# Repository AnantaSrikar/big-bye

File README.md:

# big-bye
A project that encompasses (almost) all the knowledge and skills I acquired throughout my undergraduate degree, serving as a farewell gift! 

The skills / tools I used
- Programming (C. Python, bash, etc)
- Server Setup (Web server with HTTPS by Caddy)
- Network Setup (Its currently hosted on my HomeLab)
- Soldering (Perfboard and SMD)
- PCB Desigining
- 3D Modelling (A case was supposed to be designed, didn't happen due to logistical issues)

## Components
- [Firmware](/firmware/)
- [Web Server](/web_server/)

You can find a demo of the project [here](https://youtu.be/nfPE4j3Xo48)!

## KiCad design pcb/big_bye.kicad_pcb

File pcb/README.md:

# PCB
Here are the KiCAD files for the PCB that I designed for this project.

You can find the BOM [here](bom.csv).

The ST7735 Display can be found at this [link](https://robu.in/product/1-8-inch-spi-128160-tft-lcd-display-module-pcb-arduino/).

## Schematic

The PCB looks something like this:

You can watch a demo of the project in action (with the PCB and the display) [here](https://youtu.be/nfPE4j3Xo48)!

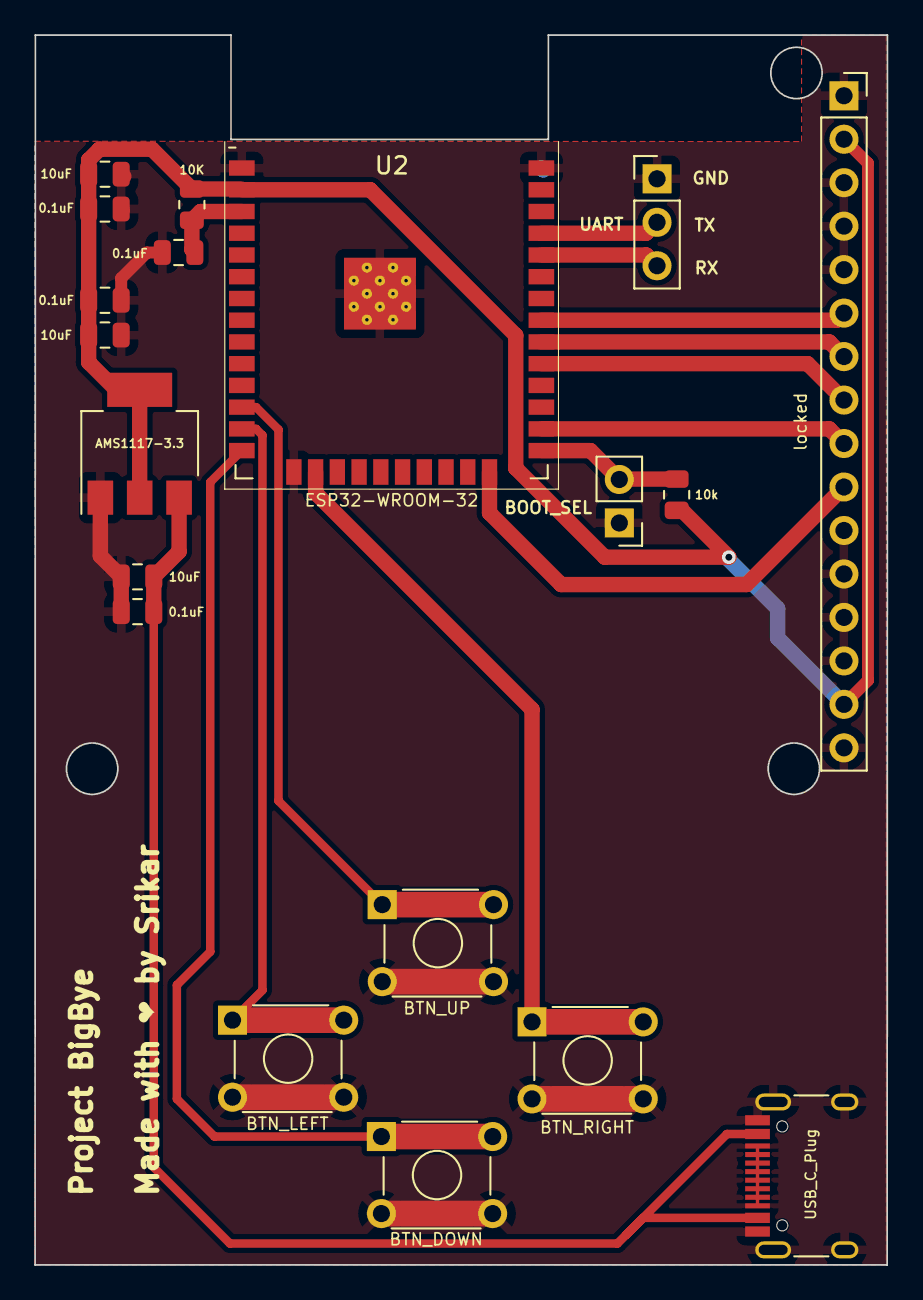
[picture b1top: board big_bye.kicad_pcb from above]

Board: 2 copper layers, 49.8 x 71.9 mm, 19 parts (0 on the bottom side), 16 nets.

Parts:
C1, C5, C7: 10uF; C_0805_2012Metric
C2, C3, C4, C6: 0.1uF; C_0805_2012Metric
J1: UART; PinHeader_1x03_P2.54mm_Vertical
J2: BOOT_SEL; PinHeader_1x02_P2.54mm_Vertical
J3: locked; PinSocket_1x16_P2.54mm_Vertical
P1: USB_C_Plug; USB_C_Receptacle_HRO_TYPE-C-31-M-12
R1: 10K; R_0805_2012Metric
R2: 10k; R_0805_2012Metric
SW1: BTN_LEFT; SW_TH_Tactile_Omron_B3F-10xx
SW2: BTN_RIGHT; SW_TH_Tactile_Omron_B3F-10xx
SW3: BTN_UP; SW_TH_Tactile_Omron_B3F-10xx
SW4: BTN_DOWN; SW_TH_Tactile_Omron_B3F-10xx
U1: AMS1117-3.3; SOT-223-3_TabPin2
U2: ESP32-WROOM-32

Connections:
+5V: C4.1, C5.1, P1.A4 (VBUS), P1.A9 (VBUS), P1.B4 (VBUS), P1.B9 (VBUS), U1.3 (VI)
BOOT: J2.2, R2.2, U2.25 (IO0)
BTN_DOWN: SW4.1, U2.14 (IO12)
BTN_LEFT: SW1.1, U2.13 (IO14)
BTN_RIGHT: SW2.1, U2.16 (IO13)
BTN_UP: SW3.1, U2.12 (IO27)
CS: J3.10, U2.24 (IO2)
DC: J3.7, U2.30 (IO18)
EN: C3.2, R1.1, U2.3 (EN)
GND: C1.2, C2.2, C3.1, C4.2, C5.2, C6.2, C7.2, J1.1, J2.1, J3.1, J3.3, J3.4, J3.5, J3.11, J3.12, J3.13, J3.14, J3.16, P1.A1 (GND), P1.A5 (CC), P1.A6 (D+), P1.A7 (D-), P1.A8 (SBU1), P1.A12 (GND), P1.B1 (GND), P1.B5 (VCONN), P1.B8 (SBU2), P1.B12 (GND), P1.S1 (SHIELD), SW1.2, SW2.2, SW3.2, SW4.2, U1.1 (GND), U2.1 (GND), U2.15 (GND), U2.38 (GND), U2.39 (GND)
MOSI: J3.8, U2.29 (IO5)
RESET: J3.6, U2.31 (IO19)
RXD: J1.3, U2.34 (RXD0/IO3)
SCLK: J3.9, U2.26 (IO4)
TXD: J1.2, U2.35 (TXD0/IO1)
VDD33: C1.1, C2.1, C6.1, C7.1, J3.2, J3.15, R1.2, R2.1, U1.2 (VO), U2.2 (VDD)

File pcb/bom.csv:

"Id";"Designator";"Footprint";"Quantity";"Designation";"Supplier and ref";
1;"R2";"R_0805_2012Metric";1;"10k";;;
2;"C7,C5,C1";"C_0805_2012Metric";3;"10uF";;;
3;"C4,C3,C2,C6";"C_0805_2012Metric";4;"0.1uF";;;
4;"P1";"USB_C_Receptacle_HRO_TYPE-C-31-M-12";1;"USB_C_Plug";;;
5;"J2";"PinHeader_1x02_P2.54mm_Vertical";1;"BOOT_SEL";;;
6;"SW3";"SW_TH_Tactile_Omron_B3F-10xx";1;"BTN_UP";;;
7;"U2";"ESP32-WROOM-32";1;"ESP32-WROOM-32";;;
8;"J1";"PinHeader_1x03_P2.54mm_Vertical";1;"UART";;;
9;"J3";"PinSocket_1x16_P2.54mm_Vertical";1;"Display_Connector";;;
10;"SW1";"SW_TH_Tactile_Omron_B3F-10xx";1;"BTN_LEFT";;;
11;"SW4";"SW_TH_Tactile_Omron_B3F-10xx";1;"BTN_DOWN";;;
12;"R1";"R_0805_2012Metric";1;"10K";;;
13;"U1";"SOT-223-3_TabPin2";1;"AMS1117-3.3";;;
14;"SW2";"SW_TH_Tactile_Omron_B3F-10xx";1;"BTN_RIGHT";;;

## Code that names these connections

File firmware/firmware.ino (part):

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// Each character width is approximately 6 pixels with text size 1
#define LTR_PXL	6

#define BTN_LEFT	14
#define BTN_RIGHT	13
#define BTN_UP		27
#define BTN_DOWN	12

#define JSON_PARSE_CAP 2048

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	displayCenter("Initialising...", Y_CENTER, true);

	// Setup BTN Inputs
	pinMode(BTN_LEFT, INPUT_PULLUP);
	pinMode(BTN_RIGHT, INPUT_PULLUP);
	pinMode(BTN_UP, INPUT_PULLUP);
	pinMode(BTN_DOWN, INPUT_PULLUP);

	// WiFi 
	WiFi.onEvent(SysProvEvent);
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
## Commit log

2023-05-28 Firmware: WiFi provisoning done - TODO: Generate QR and integrate with display
2023-05-29 Firmware: WiFi provisioning with QR done - Added necessary arduino library dependencies - Added display related configs - Added useful references
2023-05-29 Firmware: Added basic HTTP client with GET request
2023-07-03 Firmware: Added button press event - Docs: Added ESP32 flashing reference
2023-07-09 Docs: Added some basic docs
2023-07-09 Web_server: Added basic webserver
2023-07-09 Web_server: Added webserver functionality with DB
2023-07-10 Firmware: Firmware more efficient with display and web activity - Web_server: Modified DB structure for easier access on firmware - Web_server: Added get_num_msgs() endpoint for easier display on ESP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
2023-07-10 Firmware: Display message heading at centre - Switching between messages also working - TODO: Button press to interrupt later
2023-07-13 Firmware: Fixed display bug - Refactored code to have similar functions together - Added Library version in dependencies.txt - Fixed bug with message switching
2023-07-13 Firmware: Fixed word wrap bug - Added message number footer - Modified displayCenter for dynamic y-axis coords and screenwipe
2023-07-14 Firmware: Tiny bugfixes and improvements - Added BasicAuth for improved privacy - We now wait till we get an IP address to run a GET request - Improved error message display on screen
2023-07-14 Firmware: Added board reset and fixed more bugs - Removed unnecessary debug prints
2023-07-14 Firmware: Fixed bug with HTTP request
2023-08-01 Docs: Updated all READMEs
2023-08-03 PCB: Added final PCB design with more docs

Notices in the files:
firmware/firmware.ino:
@copyright Copyright (c) 2023
